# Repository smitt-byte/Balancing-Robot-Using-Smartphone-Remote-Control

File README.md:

# Balancing-Robot-Using-Smartphone-Remote-Control

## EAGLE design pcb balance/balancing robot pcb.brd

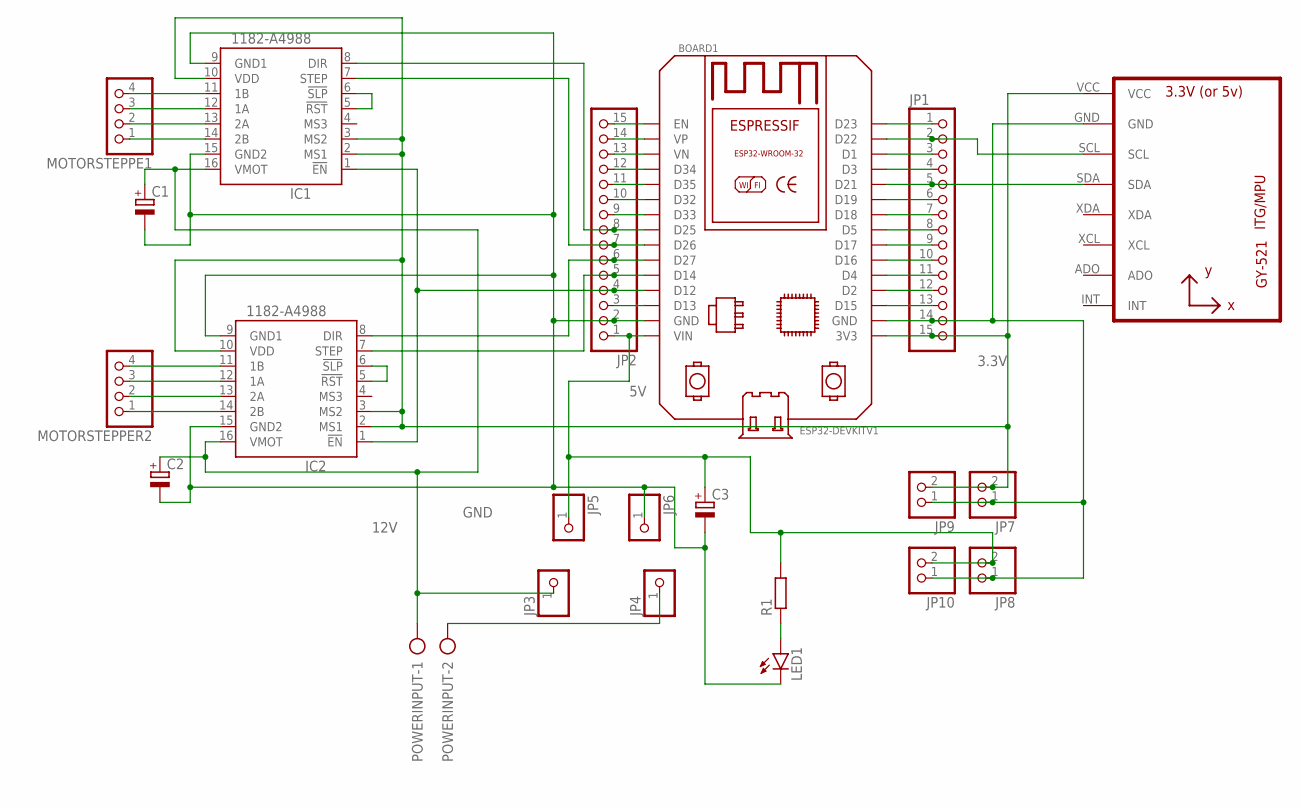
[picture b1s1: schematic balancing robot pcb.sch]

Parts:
BOARD1: ESP32DEVKITV1; ESP32-DEVKITV1
C1, C2, C3: CPOL-EUE3.5-8; E3,5-8
IC1, IC2: 1182-A4988; A4988
JP1, JP2: PINHD-1X15; 1X15
JP3, JP4, JP5, JP6: PINHD-1X1; 1X01
JP7, JP8, JP9, JP10: PINHD-1X2; 1X02
LED1: LED5MM
MOTORSTEPPE1: PINHD-1X4; 1X04
MOTORSTEPPER2: PINHD-1X4; 1X04
POWERINPUT: AK500/2-H
R1: R-EU_0204/7; 0204/7
U1: GY-521MPU6050; GY-521

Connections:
3.3V: BOARD1.3V3, IC1.2 (MS1), IC1.3 (MS2), IC1.10 (VDD), IC2.2 (MS1), IC2.3 (MS2), IC2.10 (VDD), JP1.15, JP7.2, JP9.2, U1.VCC
5V: BOARD1.VIN, C3.+, JP2.1, JP5.1, JP8.2, JP10.2, R1.2
12V: C1.+, C2.+, IC1.16 (VMOT), IC2.16 (VMOT), JP3.1, POWERINPUT.1
GND: BOARD1.GND, C1.-, C2.-, C3.-, IC1.9 (GND1), IC1.15 (GND2), IC2.9 (GND1), IC2.15 (GND2), JP2.2, JP6.1, LED1.K (C)
unnamed: BOARD1.D25, IC1.8 (DIR), JP2.8
unnamed: BOARD1.D26, IC1.7 (STEP), JP2.7
unnamed: BOARD1.D27, IC2.8 (DIR), JP2.6
unnamed: BOARD1.D14, IC2.7 (STEP), JP2.5
unnamed: IC1.14 (2B), MOTORSTEPPE1.1
unnamed: IC1.13 (2A), MOTORSTEPPE1.2
unnamed: IC1.12 (1A), MOTORSTEPPE1.3
unnamed: IC1.11 (1B), MOTORSTEPPE1.4
unnamed: IC2.14 (2B), MOTORSTEPPER2.1
unnamed: IC2.13 (2A), MOTORSTEPPER2.2
unnamed: IC2.12 (1A), MOTORSTEPPER2.3
unnamed: IC2.11 (1B), MOTORSTEPPER2.4
unnamed: BOARD1.D23, JP1.1
unnamed: BOARD1.D22, JP1.2, U1.SCL
unnamed: BOARD1.D1, JP1.3
unnamed: BOARD1.D3, JP1.4
unnamed: BOARD1.D21, JP1.5, U1.SDA
unnamed: BOARD1.D19, JP1.6
unnamed: BOARD1.D18, JP1.7
unnamed: BOARD1.D5, JP1.8
unnamed: BOARD1.D17, JP1.9
unnamed: BOARD1.D16, JP1.10
unnamed: BOARD1.D4, JP1.11
unnamed: BOARD1.D2, JP1.12
unnamed: BOARD1.D15, JP1.13
unnamed: BOARD1.GND@1 (GND), JP1.14, JP7.1, JP8.1, JP9.1, JP10.1, U1.GND
unnamed: JP4.1, POWERINPUT.2
unnamed: LED1.A, R1.1
unnamed: BOARD1.D13, JP2.3
unnamed: BOARD1.D12, IC1.1 (!EN), IC2.1 (!EN), JP2.4
unnamed: BOARD1.D33, JP2.9
unnamed: BOARD1.D32, JP2.10
unnamed: BOARD1.D35, JP2.11
unnamed: BOARD1.D34, JP2.12
unnamed: BOARD1.VN, JP2.13
unnamed: BOARD1.VP, JP2.14
unnamed: BOARD1.EN, JP2.15
unnamed: IC1.5 (!RST), IC1.6 (!SLP)
unnamed: IC2.5 (!RST), IC2.6 (!SLP)

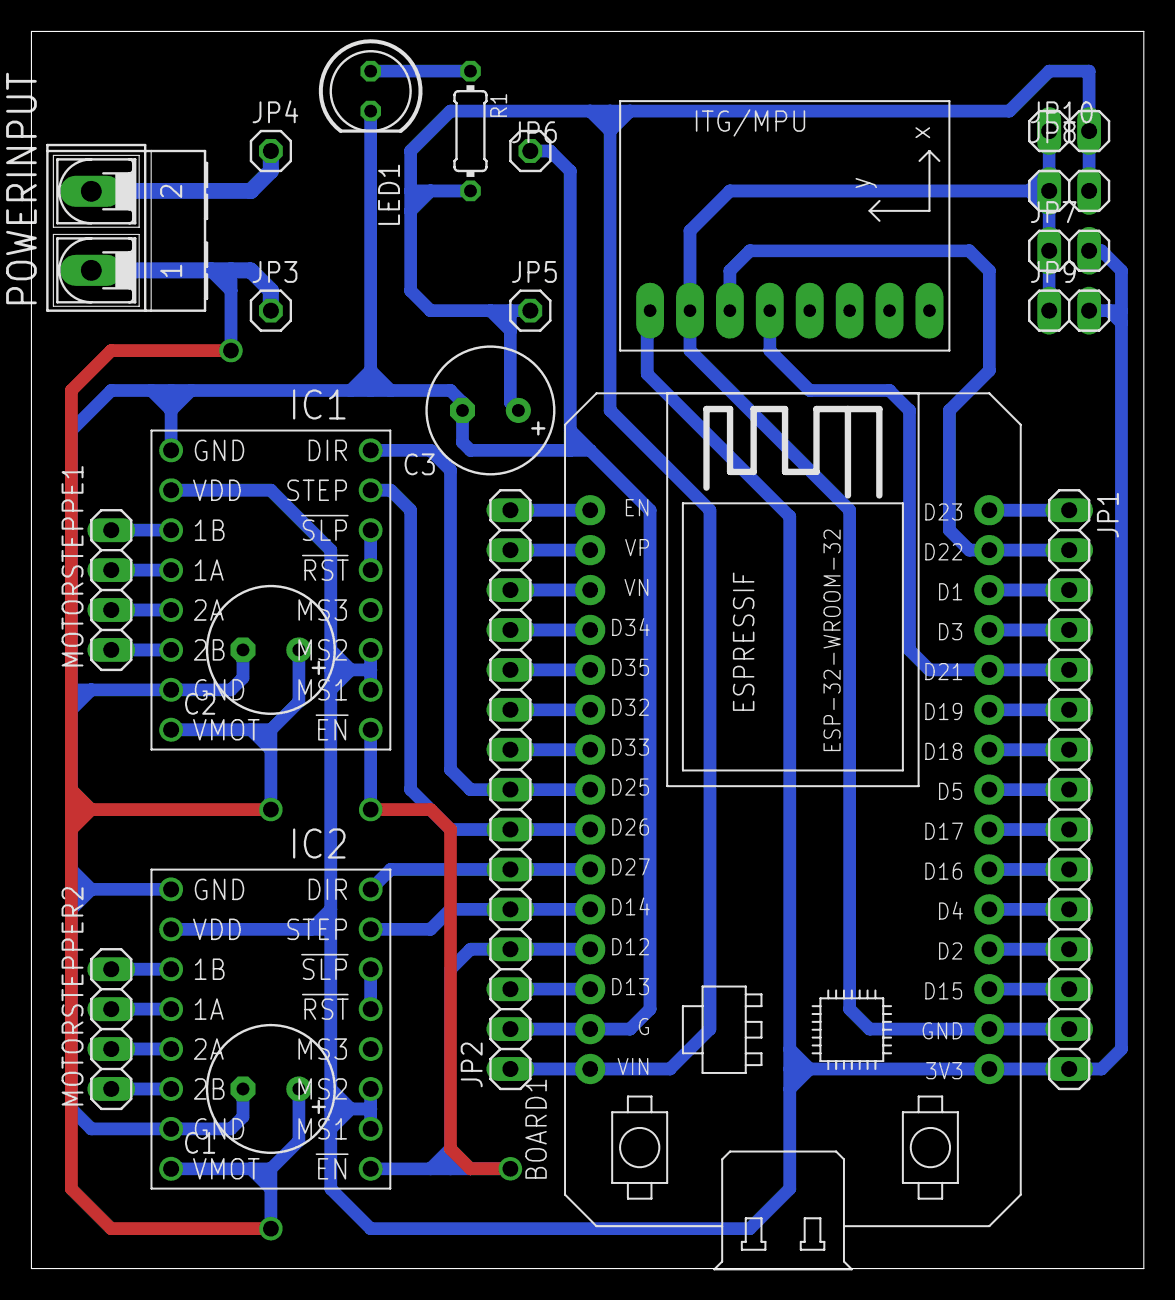
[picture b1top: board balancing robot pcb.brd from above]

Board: 2 copper layers, 70.8 x 78.7 mm, 22 parts (0 on the bottom side), 43 nets.
